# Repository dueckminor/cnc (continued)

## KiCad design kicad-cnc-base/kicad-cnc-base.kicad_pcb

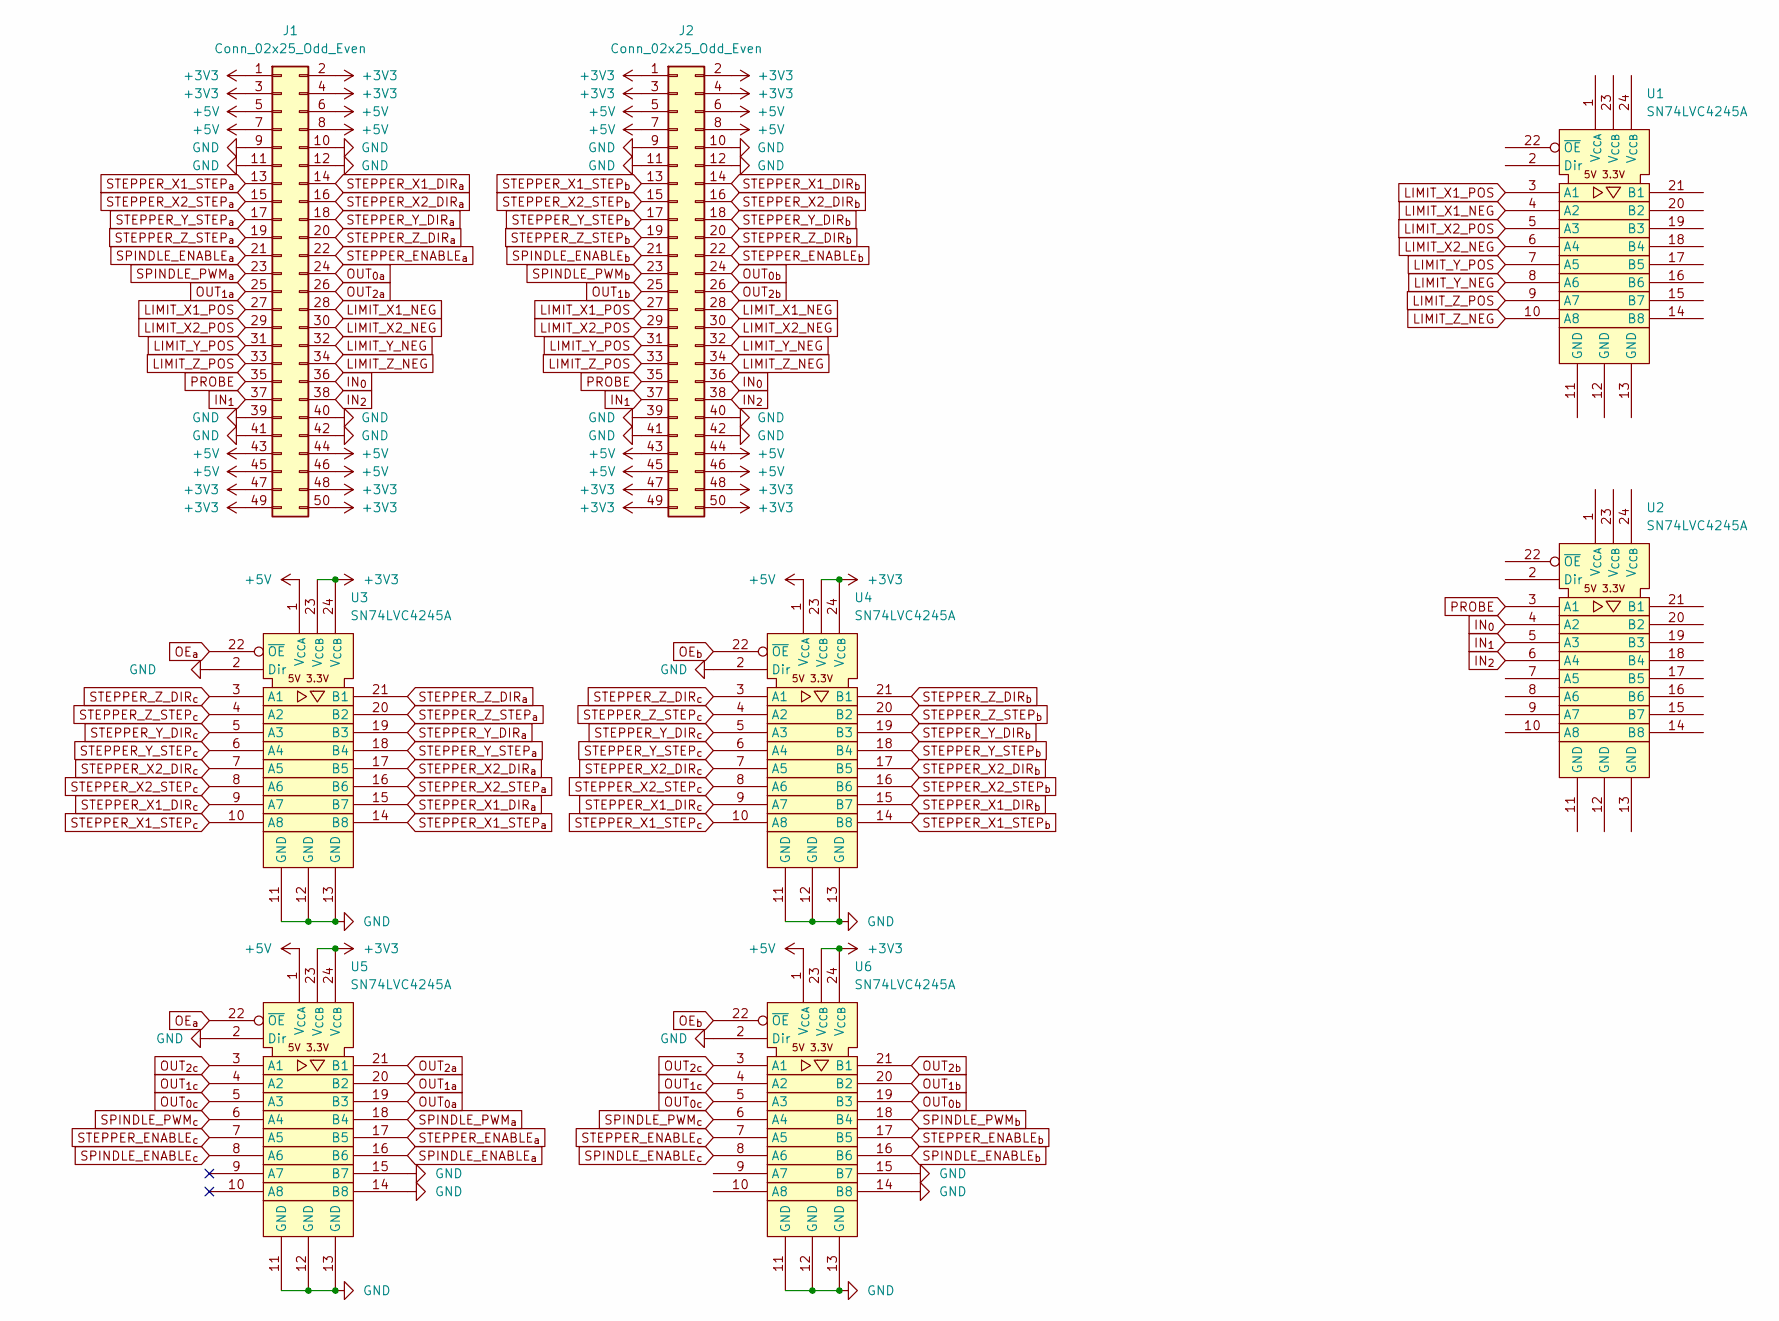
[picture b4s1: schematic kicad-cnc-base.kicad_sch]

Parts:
J1, J2: Conn_02x25_Odd_Even; PinSocket_2x25_P2.54mm_Vertical
U1, U2, U3, U4, U5, U6: SN74LVC4245A; TSSOP-24_4.4x7.8mm_P0.65mm

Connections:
+3V3: J1.1, J1.2, J1.3, J1.4, J1.47, J1.48, J1.49, J1.50, J2.1, J2.2, J2.3, J2.4, J2.47, J2.48, J2.49, J2.50, U3.23 (V_{CCB}), U3.24 (V_{CCB}), U4.23 (V_{CCB}), U4.24 (V_{CCB}), U5.23 (V_{CCB}), U5.24 (V_{CCB}), U6.23 (V_{CCB}), U6.24 (V_{CCB})
+5V: J1.5, J1.6, J1.7, J1.8, J1.43, J1.44, J1.45, J1.46, J2.5, J2.6, J2.7, J2.8, J2.43, J2.44, J2.45, J2.46, U3.1 (V_{CCA}), U4.1 (V_{CCA}), U5.1 (V_{CCA}), U6.1 (V_{CCA})
GND: J1.9, J1.10, J1.11, J1.12, J1.39, J1.40, J1.41, J1.42, J2.9, J2.10, J2.11, J2.12, J2.39, J2.40, J2.41, J2.42, U3.2 (Dir), U3.11 (GND), U3.12 (GND), U3.13 (GND), U4.2 (Dir), U4.11 (GND), U4.12 (GND), U4.13 (GND), U5.2 (Dir), U5.11 (GND), U5.12 (GND), U5.13 (GND), U5.14 (B8), U5.15 (B7), U6.2 (Dir), U6.11 (GND), U6.12 (GND), U6.13 (GND), U6.14 (B8), U6.15 (B7)
IN_{0}: J1.36, J2.36, U2.4 (A2)
IN_{1}: J1.37, J2.37, U2.5 (A3)
IN_{2}: J1.38, J2.38, U2.6 (A4)
LIMIT_X1_NEG: J1.28, J2.28, U1.4 (A2)
LIMIT_X1_POS: J1.27, J2.27, U1.3 (A1)
LIMIT_X2_NEG: J1.30, J2.30, U1.6 (A4)
LIMIT_X2_POS: J1.29, J2.29, U1.5 (A3)
LIMIT_Y_NEG: J1.32, J2.32, U1.8 (A6)
LIMIT_Y_POS: J1.31, J2.31, U1.7 (A5)
LIMIT_Z_NEG: J1.34, J2.34, U1.10 (A8)
LIMIT_Z_POS: J1.33, J2.33, U1.9 (A7)
OE_{a}: U3.22 (~OE), U5.22 (~OE)
OE_{b}: U4.22 (~OE), U6.22 (~OE)
OUT_{0}_{a}: J1.24, U5.19 (B3)
OUT_{0}_{b}: J2.24, U6.19 (B3)
OUT_{0}_{c}: U5.5 (A3), U6.5 (A3)
OUT_{1}_{a}: J1.25, U5.20 (B2)
OUT_{1}_{b}: J2.25, U6.20 (B2)
OUT_{1}_{c}: U5.4 (A2), U6.4 (A2)
OUT_{2}_{a}: J1.26, U5.21 (B1)
OUT_{2}_{b}: J2.26, U6.21 (B1)
OUT_{2}_{c}: U5.3 (A1), U6.3 (A1)
PROBE: J1.35, J2.35, U2.3 (A1)
SPINDLE_ENABLE_{a}: J1.21, U5.16 (B6)
SPINDLE_ENABLE_{b}: J2.21, U6.16 (B6)
SPINDLE_ENABLE_{c}: U5.8 (A6), U6.8 (A6)
SPINDLE_PWM_{a}: J1.23, U5.18 (B4)
SPINDLE_PWM_{b}: J2.23, U6.18 (B4)
SPINDLE_PWM_{c}: U5.6 (A4), U6.6 (A4)
STEPPER_ENABLE_{a}: J1.22, U5.17 (B5)
STEPPER_ENABLE_{b}: J2.22, U6.17 (B5)
STEPPER_ENABLE_{c}: U5.7 (A5), U6.7 (A5)
STEPPER_X1_DIR_{a}: J1.14, U3.15 (B7)
STEPPER_X1_DIR_{b}: J2.14, U4.15 (B7)
STEPPER_X1_DIR_{c}: U3.9 (A7), U4.9 (A7)
STEPPER_X1_STEP_{a}: J1.13, U3.14 (B8)
STEPPER_X1_STEP_{b}: J2.13, U4.14 (B8)
STEPPER_X1_STEP_{c}: U3.10 (A8), U4.10 (A8)
STEPPER_X2_DIR_{a}: J1.16, U3.17 (B5)
STEPPER_X2_DIR_{b}: J2.16, U4.17 (B5)
STEPPER_X2_DIR_{c}: U3.7 (A5), U4.7 (A5)
STEPPER_X2_STEP_{a}: J1.15, U3.16 (B6)
STEPPER_X2_STEP_{b}: J2.15, U4.16 (B6)
STEPPER_X2_STEP_{c}: U3.8 (A6), U4.8 (A6)
STEPPER_Y_DIR_{a}: J1.18, U3.19 (B3)
STEPPER_Y_DIR_{b}: J2.18, U4.19 (B3)
STEPPER_Y_DIR_{c}: U3.5 (A3), U4.5 (A3)
STEPPER_Y_STEP_{a}: J1.17, U3.18 (B4)
STEPPER_Y_STEP_{b}: J2.17, U4.18 (B4)
STEPPER_Y_STEP_{c}: U3.6 (A4), U4.6 (A4)
STEPPER_Z_DIR_{a}: J1.20, U3.21 (B1)
STEPPER_Z_DIR_{b}: J2.20, U4.21 (B1)
STEPPER_Z_DIR_{c}: U3.3 (A1), U4.3 (A1)
STEPPER_Z_STEP_{a}: J1.19, U3.20 (B2)
STEPPER_Z_STEP_{b}: J2.19, U4.20 (B2)
STEPPER_Z_STEP_{c}: U3.4 (A2), U4.4 (A2)

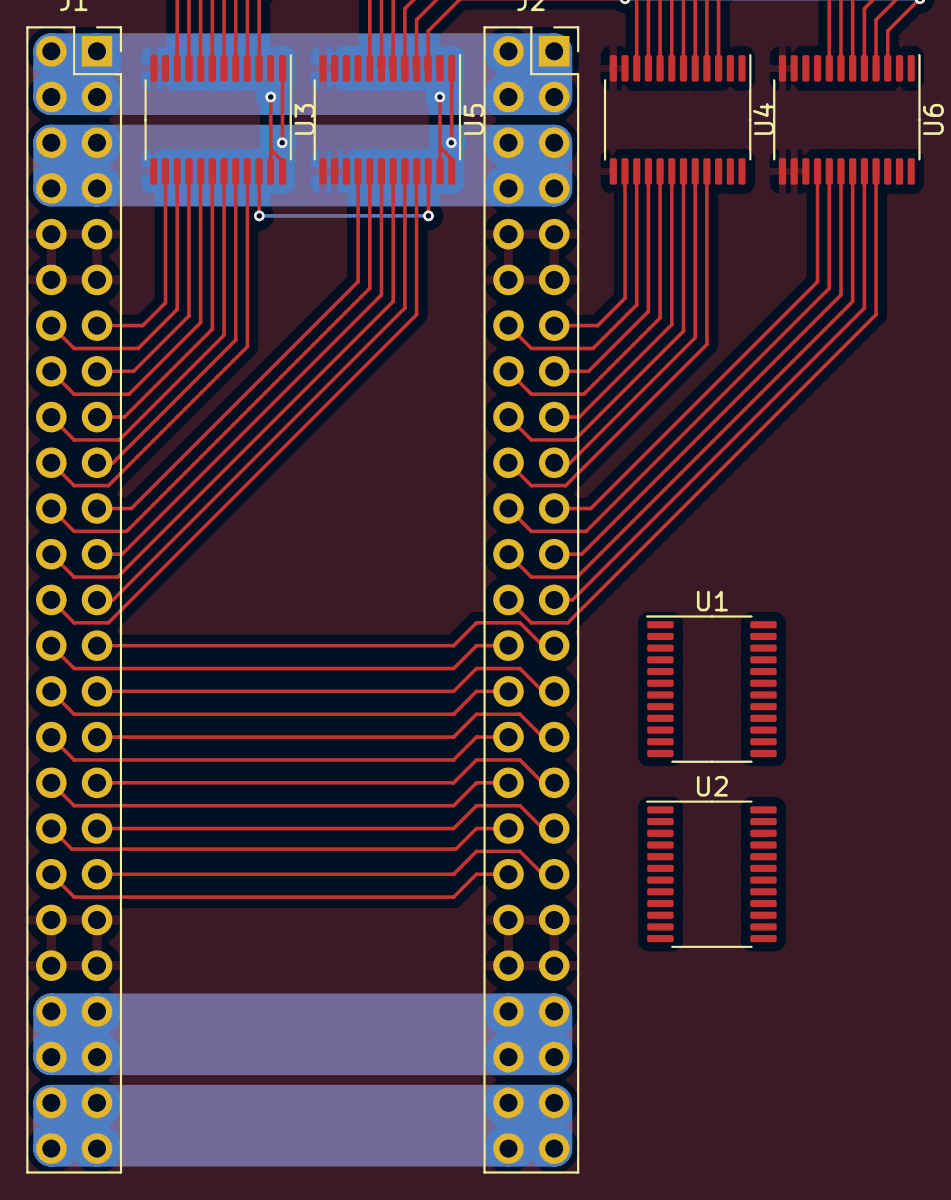
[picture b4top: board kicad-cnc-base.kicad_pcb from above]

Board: 2 copper layers, 8 parts (0 on the bottom side), 59 nets.

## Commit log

2022-01-02 esp32_pins
2022-03-19 added kicad files
2022-03-21 started with the base pcb
2022-03-30 updated boards
2022-04-08 updated PCBs
2022-04-08 docu
2022-04-14 added fluidnc config file
2022-08-27 Added halter
2022-08-27 updated kicad-cnc-esp32
